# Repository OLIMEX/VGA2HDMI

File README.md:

# VGA2HDMI
VGA to HDMI converter

## Features

* VGA input connector
* HDMI output connector
* USB-C for power supply
* Power supply status LED
* VGA signal status LED
* HDMI signal status LED
* Dimensions 51x33mm
* 2 mount holes

## Licenses

* Hardware is released under CERN Open Hardware Licence Version 2 - Strongly Reciprocal, all silkscreen credits to Olimex should remain;
* Documentation is released under CC BY-SA 4.0

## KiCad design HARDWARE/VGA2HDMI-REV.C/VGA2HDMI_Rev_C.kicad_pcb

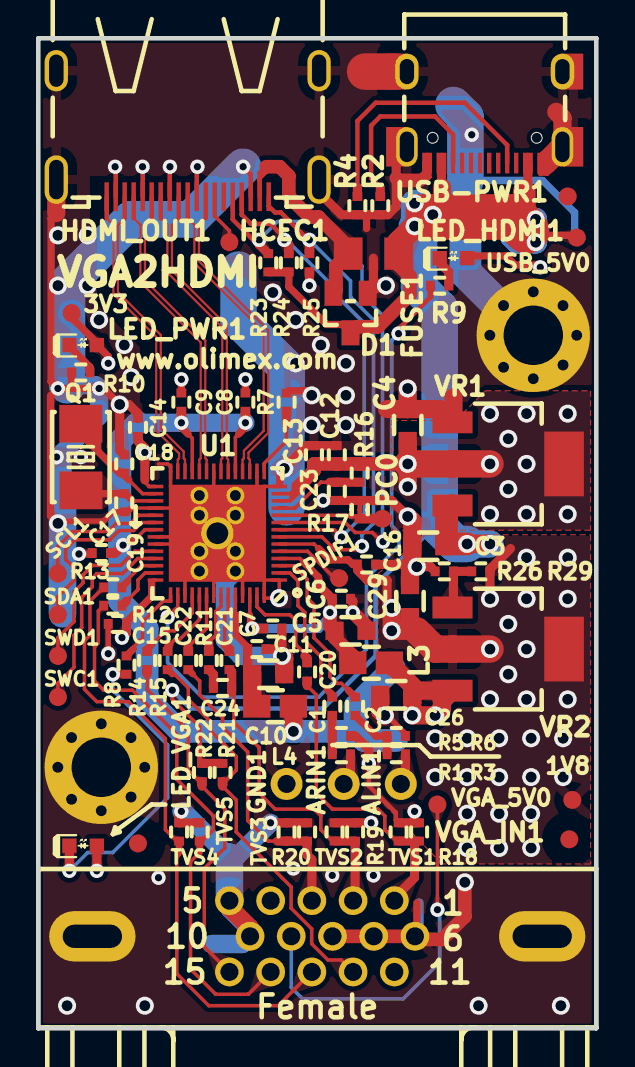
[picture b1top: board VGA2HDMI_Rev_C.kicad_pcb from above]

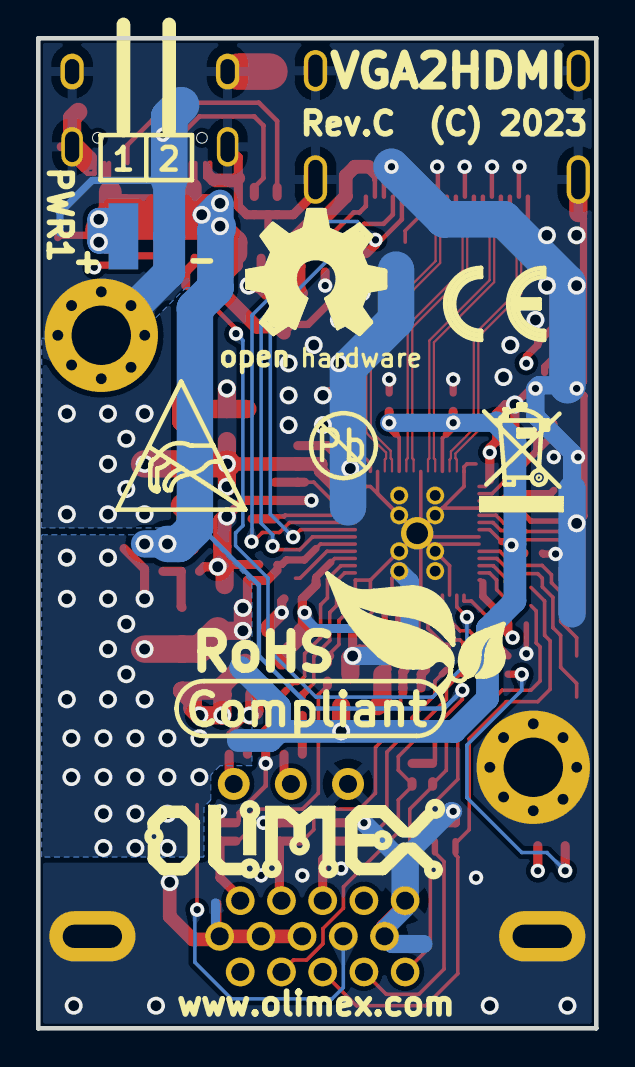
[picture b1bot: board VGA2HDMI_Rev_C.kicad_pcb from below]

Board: 4 copper layers, 31.0 x 55.0 mm, 99 parts (8 on the bottom side), 60 nets.

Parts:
1V8, 3V3: TESTPAD; TESTPAD_40-ROUND
ALIN1: TESTPAD; TEST_PAD_40x70_Round
ARIN1: TESTPAD; TEST_PAD_40x70_Round
C1, C2: 4.7uF/X5R/20%/10V/C0402; C_0402_5MIL_DWS
C3, C4, C5, C10, C29: 22uF/6.3V/20%/X5R/C0603; C_0603_5MIL_DWS
C6, C7, C8, C9, C11, C12, C13, C14, C15, C16, C17, C23: 100nF/10V/20%/X5R/C0402; C_0402_5MIL_DWS
C18, C19: 33pF/50V/5%/C0G/C0402; C_0402_5MIL_DWS
C20, C21, C22: 47nF/50V/10%/X7R/C0402; C_0402_5MIL_DWS
C24: NA(1nF/C0402); C_0402_5MIL_DWS
C26: NA(22uF/6.3V/20%/X5R/C0603); C_0603_5MIL_DWS
D1: CH213K(SOT23-3); SOT23-3
FID1, FID2: Fiducial; Fiducial1x3
FID3: Fiducial; Fiducial1x3_Paste
FUSE1: NA(FSMD035-1206); FUSE-1206
GND1: TESTPAD; TEST_PAD_40x70_Round
HCEC1: TESTPAD; TESTPAD_40-ROUND
HDMI_OUT1: HDMI-SWM-19; HDMI-SWM-19_Paste
L3, L4: IND/600OHM/2A/UPZ2012E-601-2R0TF/L0805; L_0805_5MIL_DWS
LED_HDMI1: LED/RED/0603; LED_0603_KA
LED_PWR1: LED/RED/0603; LED_0603_KA
LED_VGA1: LED/RED/0603; LED_0603_KA
Logo_OLIMEX_TB-Bottom: Logo_OLIMEX_TB
Mount-Hole-3.3mm1, Mount-Hole-3.3mm3: Mounting_hole_Shield_3.3mm
PC0: TESTPAD; TESTPAD_40-ROUND
PWR1: NA(HN1x2(SMD)_H-WX-1x2-LF); HN1x2(SMD)_H-WX-1x2-LF
Q1: Q24.576MHz/20pF/20ppm/2P/5x3.2mm; HCX-4S_2Pins_5.0x3.2mm_TEST
R1, R3, R5, R6, R21, R22, R23, R24: 10k/R0402; R_0402_5MIL_DWS
R2, R4: 5.1k/1%/R0402; R_0402_5MIL_DWS
R7: 1k/1%/R0402; R_0402_5MIL_DWS
R8, R9, R10: 2.2k/R0402; R_0402_5MIL_DWS
R11: NA(4.7k/R0402); R_0402_5MIL_DWS
R12, R13, R14, R15, R18, R19, R20: 75R/1%/R0402; R_0402_5MIL_DWS
R16, R25: NA(10k/R0402); R_0402_5MIL_DWS
R17: 0R/R0402/Board_Mounted; R_0402_5MIL_0R(Board_Mounted)
R26: 100R/1%/R0402; R_0402_5MIL_DWS
R29: 220R/1%/R0402; R_0402_5MIL_DWS
SCL1: TESTPAD; TESTPAD_40-ROUND
SDA1: TESTPAD; TESTPAD_40-ROUND
SPDIF1: TESTPAD; TESTPAD_40-ROUND
SWC1: TESTPAD; TESTPAD_40-ROUND
SWD1: TESTPAD; TESTPAD_40-ROUND
Sign_Antistatic: Sign_Antistatic
Sign_CE: CE_Sign
Sign_OSHW_8x8: Sign_OSHW_8x8
Sign_PB-Free: Sign_PB-Free
Sign_RecycleBin: Sign_RecycleBin; Sign_RecycleBin_1
Sign_RoHS: Sign_RoHS; Sign_RoHS_1
TVS1, TVS2, TVS3, TVS4, TVS5: NA(GG0402052R542P); D_0402_5MIL_DWS
U1: CV8986(QFN56_7x7mm); QFN56_7x7_Pitch_0.4mm_EPad_5.4x5.4mm
USB-PWR1: USB-C-16P-F(A40-00119-A52-12); USB2.0_TYPE-C(A40-00119-A52-12)_Paste
USB_5V0: TESTPAD; TESTPAD_40-ROUND
VGA_5V0: TESTPAD; TESTPAD_40-ROUND
VGA_IN1: HDR15-3.08-14.5T/VGA15/14.5mm; VGA15-F(HDR15-3.08-14.5T)_DrillSlot
VR1: LD1117AG-33-AA3-A-R; SOT223
VR2: LD1117AG-AD-AA3-A-R; SOT223

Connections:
+1.8V: 1V8.1 (Pad), C8.1, C9.1, C16.1, C17.1, C29.1, L4.1, R29.2, U1.6 (DVDD18), U1.19 (AV18H), U1.25 (AV18H), U1.35 (DVDD18), VR2.2 (OUT)
+3.3V: 3V3.1 (Pad), C4.1, C12.1, C13.1, C14.1, C15.1, C26.1, L3.1, LED_HDMI1.2 (A), LED_PWR1.2 (A), LED_VGA1.2 (A), R16.2, U1.12 (VDD33), U1.13 (VDD33), U1.29 (DV33), U1.42 (DV33), VR1.2 (OUT), VR2.3 (IN)
+5V_USB: C3.1, D1.3 (VI+), FUSE1.1, PWR1.1, R21.1, R22.1, R23.1, R24.1, USB-PWR1.A4 (VBUS), USB-PWR1.A9 (VBUS), USB-PWR1.B4 (VBUS), USB-PWR1.B9 (VBUS), USB_5V0.1 (Pad), VR1.3 (IN)
/AV18: C10.1, C11.1, L4.2, U1.52 (AV18)
/AV33: C5.1, C6.1, C7.1, L3.2, U1.4 (AV33), U1.54 (AV33)
/BLUE_IN: C22.1, R20.2, TVS3.2 (IO2), VGA_IN1.3 (Blue)
/GREEN_IN: C21.1, C24.1, R19.2, TVS2.2 (IO2), VGA_IN1.2 (Green)
/HDMI_5V: D1.2 (VO-), FUSE1.2, HDMI_OUT1.18
/HDMI_DP: R9.2, U1.44 (HDMIDP)
/HDMI_HPD: HDMI_OUT1.19, R25.2, U1.7 (HPD)
/HDMI_SCL: HDMI_OUT1.15, R23.2, U1.9 (DDC_SCL)
/HDMI_SDA: HDMI_OUT1.16, R24.2, U1.8 (DDC_SDA)
/HDMI_TX0+: HDMI_OUT1.7, U1.21 (TX0P)
/HDMI_TX0-: HDMI_OUT1.9, U1.20 (TX0N)
/HDMI_TX1+: HDMI_OUT1.4, U1.24 (TX1P)
/HDMI_TX1-: HDMI_OUT1.6, U1.23 (TX1N)
/HDMI_TX2+: HDMI_OUT1.1, U1.27 (TX2P)
/HDMI_TX2-: HDMI_OUT1.3, U1.26 (TX2N)
/HDMI_TXC+: HDMI_OUT1.10, U1.18 (TXCP)
/HDMI_TXC-: HDMI_OUT1.12, U1.17 (TXCN)
/HSync_IN: R13.2, TVS4.2 (IO2), VGA_IN1.13 (HSync)
/RED_IN: C20.1, R18.2, TVS1.2 (IO2), VGA_IN1.1 (Red)
/VGA_DP: R8.2, U1.43 (VGADP)
/VGA_SCL: R14.2, R22.2, VGA_IN1.15 (ID3/SCL)
/VGA_SDA: R15.2, R21.2, VGA_IN1.12 (ID1/SDA)
/VSync_IN: R12.2, TVS5.2 (IO2), VGA_IN1.14 (VSync)
GND: C3.2, C4.2, C5.2, C6.2, C7.2, C8.2, C9.2, C10.2, C11.2, C12.2, C13.2, C14.2, C15.2, C16.2, C17.2, C18.2, C19.2, C23.1, C26.2, C29.2, D1.1 (GND), GND1.1 (Pad), HDMI_OUT1.0 (20), HDMI_OUT1.2, HDMI_OUT1.5, HDMI_OUT1.8, HDMI_OUT1.11, HDMI_OUT1.17, Mount-Hole-3.3mm1.GND1, Mount-Hole-3.3mm3.GND1, PWR1.2, R2.1, R4.1, R5.2, R6.2, R7.1, R10.2, R17.2, R18.1, R19.1, R20.1, R25.1, R26.1, TVS1.1 (IO1), TVS2.1 (IO1), TVS3.1 (IO1), TVS4.1 (IO1), TVS5.1 (IO1), U1.1 (AVSS), U1.14 (VSS), U1.16 (AVSS), U1.22 (AVSS), U1.28 (AVSS), U1.32 (DVSS), U1.36 (PA11), U1.37 (PA12), U1.45 (GND), U1.49 (AVSS), U1.53 (AVSS), U1.56 (AVSS), U1.57 (EPAD), USB-PWR1.0 (SHELL), USB-PWR1.A1 (GND), USB-PWR1.A12 (GND), USB-PWR1.B1 (GND), USB-PWR1.B12 (GND), VGA_IN1.5 (GND), VGA_IN1.6 (Red_RTN), VGA_IN1.7 (Green_RTN), VGA_IN1.8 (Blue_RTN), VGA_IN1.10 (GND), VGA_IN1.16 (Shield1), VGA_IN1.17 (Shield2), VR1.1 (ADJ/GND)
unnamed: ALIN1.1 (Pad), R3.2
unnamed: ARIN1.1 (Pad), R1.2
unnamed: C1.1, R1.1, R5.1
unnamed: C2.1, R3.1, R6.1
unnamed: C24.2, R11.2
unnamed: HCEC1.1 (Pad), HDMI_OUT1.13
unnamed: LED_HDMI1.1 (K), R9.1
unnamed: LED_PWR1.1 (K), R10.1
unnamed: LED_VGA1.1 (K), R8.1
unnamed: C2.2, U1.3 (ALIN)
unnamed: C1.2, U1.2 (ARIN)
unnamed: C22.2, U1.48 (BIN)
unnamed: C21.2, U1.51 (GIN)
unnamed: R13.1, U1.40 (HS_IN)
unnamed: C23.2, R16.1, U1.11 (NRST)
unnamed: PC0.1 (Pad), R17.1, U1.10 (PC0)
unnamed: R7.2, U1.15 (REXT)
unnamed: C20.2, U1.55 (RIN)
unnamed: SCL1.1 (Pad), U1.33 (SCL)
unnamed: SDA1.1 (Pad), U1.34 (SDA)
unnamed: R11.1, U1.50 (SOG0)
unnamed: SPDIF1.1 (Pad), U1.5 (SPDIF)
unnamed: SWC1.1 (Pad), U1.39 (SWCLK)
unnamed: SWD1.1 (Pad), U1.38 (SWDIO)
unnamed: R14.1, U1.46 (VGA_SCL)
unnamed: R15.1, U1.47 (VGA_SDA)
unnamed: R12.1, U1.41 (VS_IN)
unnamed: C18.1, Q1.1, U1.30 (XTI)
unnamed: C19.1, Q1.2, U1.31 (XTO)
unnamed: R4.2, USB-PWR1.A5 (CC1)
unnamed: R2.2, USB-PWR1.B5 (CC2)
unnamed: VGA_5V0.1 (Pad), VGA_IN1.9 (Key/PWR)
unnamed: R26.2, R29.1, VR2.1 (ADJ/GND)

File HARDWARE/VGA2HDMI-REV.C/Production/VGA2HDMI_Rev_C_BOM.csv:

Quantity,Value,Footprint,Reference
2,4.7uF/X5R/20%/10V/C0402,C_0402_5MIL_DWS,"C1, C2"
5,22uF/6.3V/20%/X5R/C0603,C_0603_5MIL_DWS,"C3, C4, C5, C10, C29"
12,100nF/10V/20%/X5R/C0402,C_0402_5MIL_DWS,"C6, C7, C8, C9, C11, C12, C13, C14, C15, C16, C17, C23"
2,33pF/50V/5%/C0G/C0402,C_0402_5MIL_DWS,"C18, C19"
3,47nF/50V/10%/X7R/C0402,C_0402_5MIL_DWS,"C20, C21, C22"
1,CH213K(SOT23-3),SOT23-3,D1
1,HDMI-SWM-19,HDMI-SWM-19_Paste,HDMI_OUT1
2, IND/600OHM/2A/UPZ2012E-601-2R0TF/L0805,L_0805_5MIL_DWS,"L3, L4"
3,LED/RED/0603,LED_0603_KA,"LED_HDMI1, LED_PWR1, LED_VGA1"
1,Q24.576MHz/20pF/20ppm/2P/5x3.2mm,HCX-4S_2Pins_5.0x3.2mm_TEST,Q1
8,10k/R0402,R_0402_5MIL_DWS,"R1, R3, R5, R6, R21, R22, R23, R24"
2,5.1k/1%/R0402,R_0402_5MIL_DWS,"R2, R4"
1,1k/1%/R0402,R_0402_5MIL_DWS,R7
3,2.2k/R0402,R_0402_5MIL_DWS,"R8, R9, R10"
7,75R/1%/R0402,R_0402_5MIL_DWS,"R12, R13, R14, R15, R18, R19, R20"
1,100R/1%/R0402,R_0402_5MIL_DWS,R26
1,220R/1%/R0402,R_0402_5MIL_DWS,R29
1,CV8986(QFN56_7x7mm),QFN56_7x7_Pitch_0.4mm_EPad_5.4x5.4mm,U1
1,USB-C-16P-F(A40-00119-A52-12),USB2.0_TYPE-C(A40-00119-A52-12)_Paste,USB-PWR1
1,HDR15-3.08-14.5T/VGA15/14.5mm,VGA15-F(HDR15-3.08-14.5T)_DrillSlot,VGA_IN1
1,LD1117AG-33-AA3-A-R,SOT223,VR1
1,LD1117AG-AD-AA3-A-R,SOT223,VR2

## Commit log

2024-03-19 initial upload

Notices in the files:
HARDWARE/VGA2HDMI-REV.C/VGA2HDMI_Rev_C.kicad_pcb:
(C) 2023
